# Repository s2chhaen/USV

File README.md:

Unmanned Surface Vehicle (USV)
# USV-Projekt

Im Projekt USV entwickeln Studenten unterschiedlicher Fachbereiche ein autonomes Wasserfahrzeug, welches eine vorgegebene Route fährt. Dabei müssen Kollisionen mit bewegten und unbewegten Hindernissen vermieden werden.

(c) 2023 Joe.G

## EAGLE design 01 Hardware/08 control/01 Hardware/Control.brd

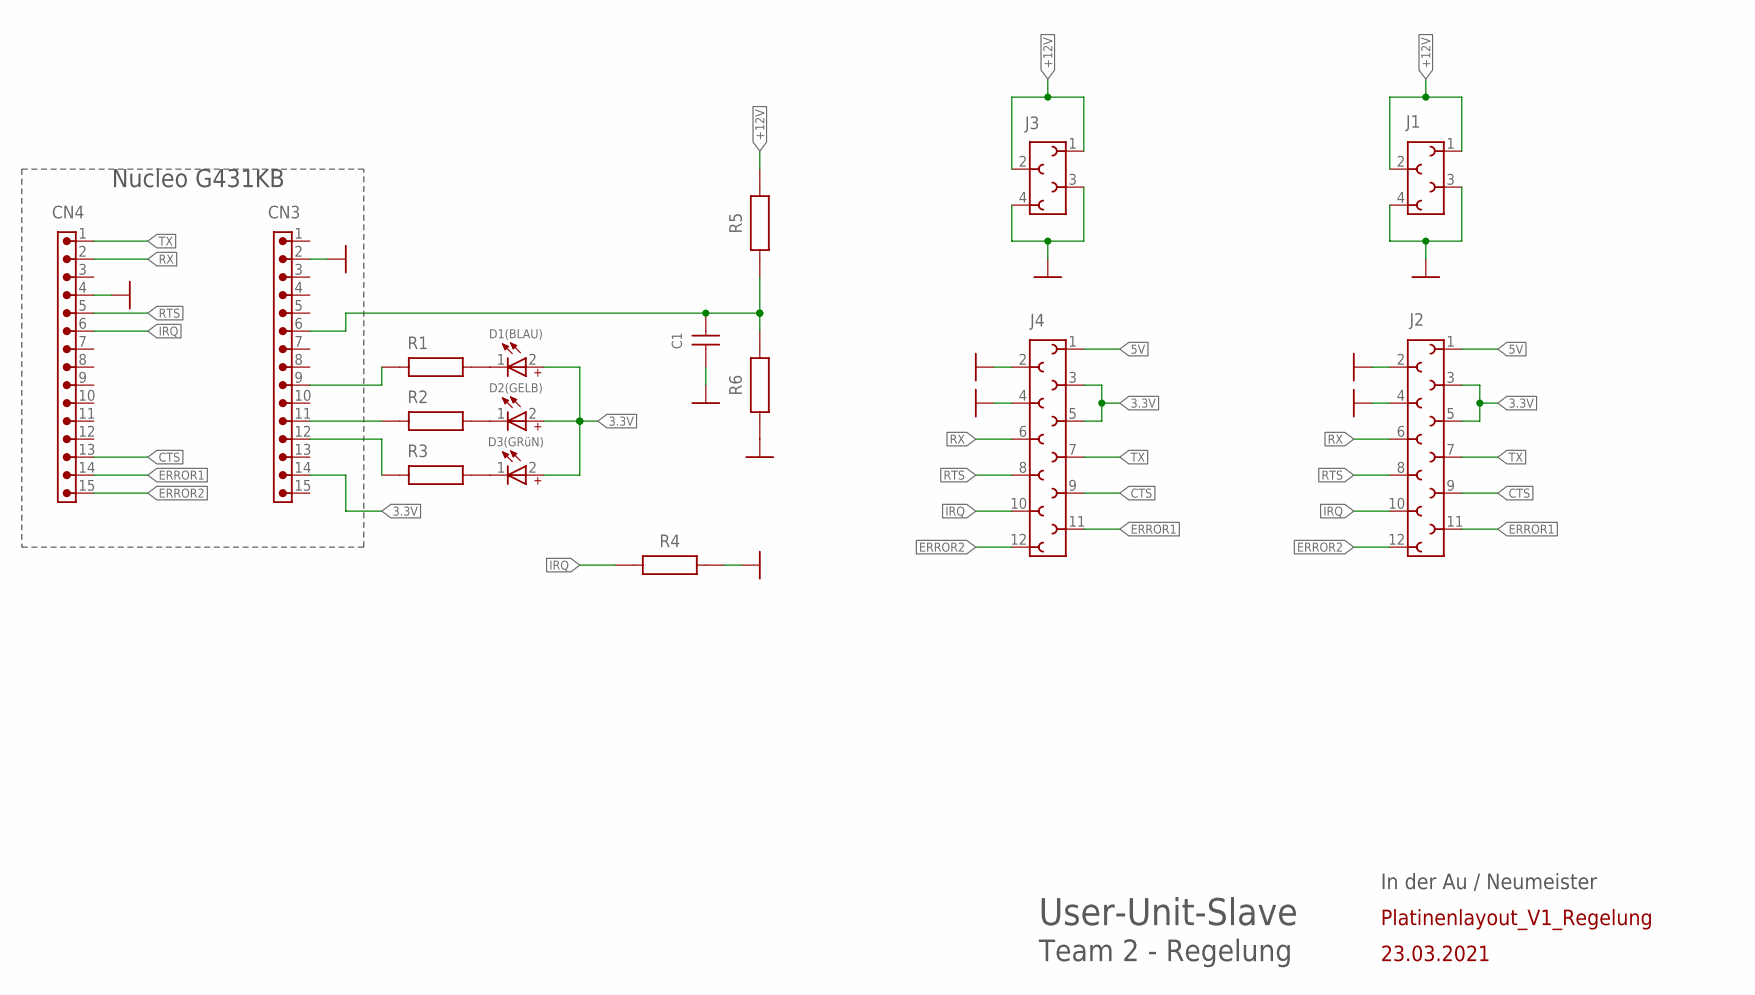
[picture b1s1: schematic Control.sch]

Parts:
C1: 10 nF; WCAP-CSGP_1206_H1.25
CN3, CN4: 61301511121
D1(BLAU): WL-TMRC_3MM_151031SS06000_WITHOUTSTOPPER; WL-TMRC_3MM
D2(GELB): WL-TMRC_3MM_151031YS06000_WITHOUTSTOPPER; WL-TMRC_3MM
D3(GRüN): WL-TMRC_3MM_151031VS06000_WITHOUTSTOPPER; WL-TMRC_3MM
J1: 6100XX11921_61000411921; 61000411921
J2: 6100XX11921_61001211921; 61001211921
J3: 690367290476
J4: 690367291276
R1, R2, R3, R5, R6: 1Ohm; WRIS-KSKE_0805_2.0X1.25X0.6(LXWXH)
R4: 0.1Ohm; WRIS-KSKE_0805_2.0X1.25X0.6(LXWXH)

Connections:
3.3V: CN3.14, D1(BLAU).2 (+), D2(GELB).2 (+), D3(GRüN).2 (+), J2.3, J2.5, J4.3, J4.5
5V: J2.1, J4.1
+12V: J1.1, J1.2, J3.1, J3.2, R5.2
ADC-INPUT: C1.2, CN3.6, R5.1, R6.2
CTS: CN4.13, J2.9, J4.9
ERROR1: CN4.14, J2.11, J4.11
ERROR2: CN4.15, J2.12, J4.12
GND: C1.1, CN3.2, CN4.4, J1.3, J1.4, J2.2, J2.4, J3.3, J3.4, J4.2, J4.4, R4.2, R6.1
GPIO_D1: CN3.9, R1.1
GPIO_D2: CN3.11, R2.1
GPIO_D3: CN3.12, R3.1
IRQ: CN4.6, J2.10, J4.10, R4.1
unnamed: D1(BLAU).1 (-), R1.2
unnamed: D2(GELB).1 (-), R2.2
unnamed: D3(GRüN).1 (-), R3.2
RTS: CN4.5, J2.8, J4.8
RX: CN4.2, J2.6, J4.6
TX: CN4.1, J2.7, J4.7

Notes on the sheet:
Nucleo G431KB
Team 2 - Regelung
User-Unit-Slave
In der Au / Neumeister
Platinenlayout_V1_Regelung
23.03.2021

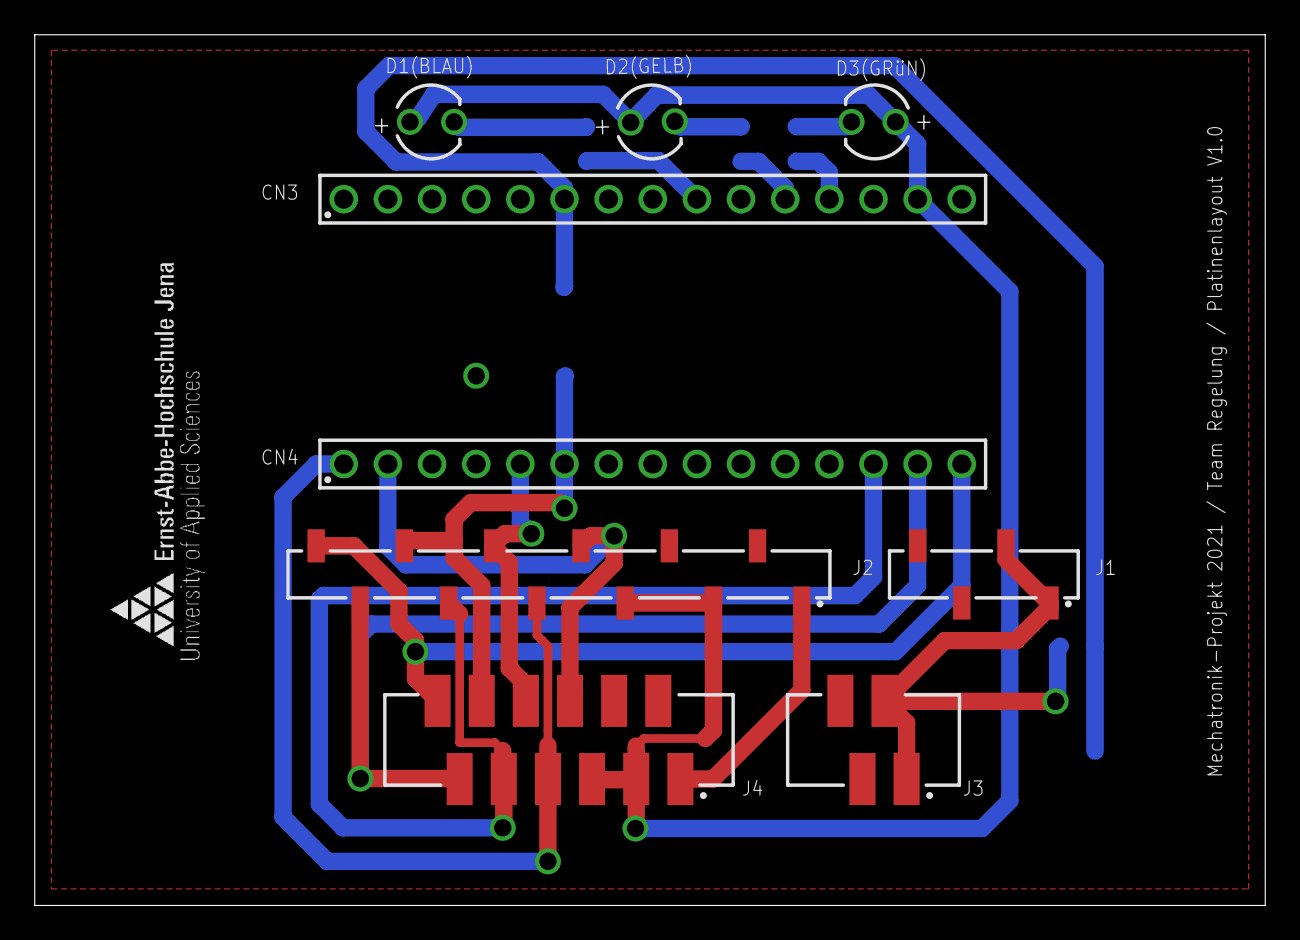
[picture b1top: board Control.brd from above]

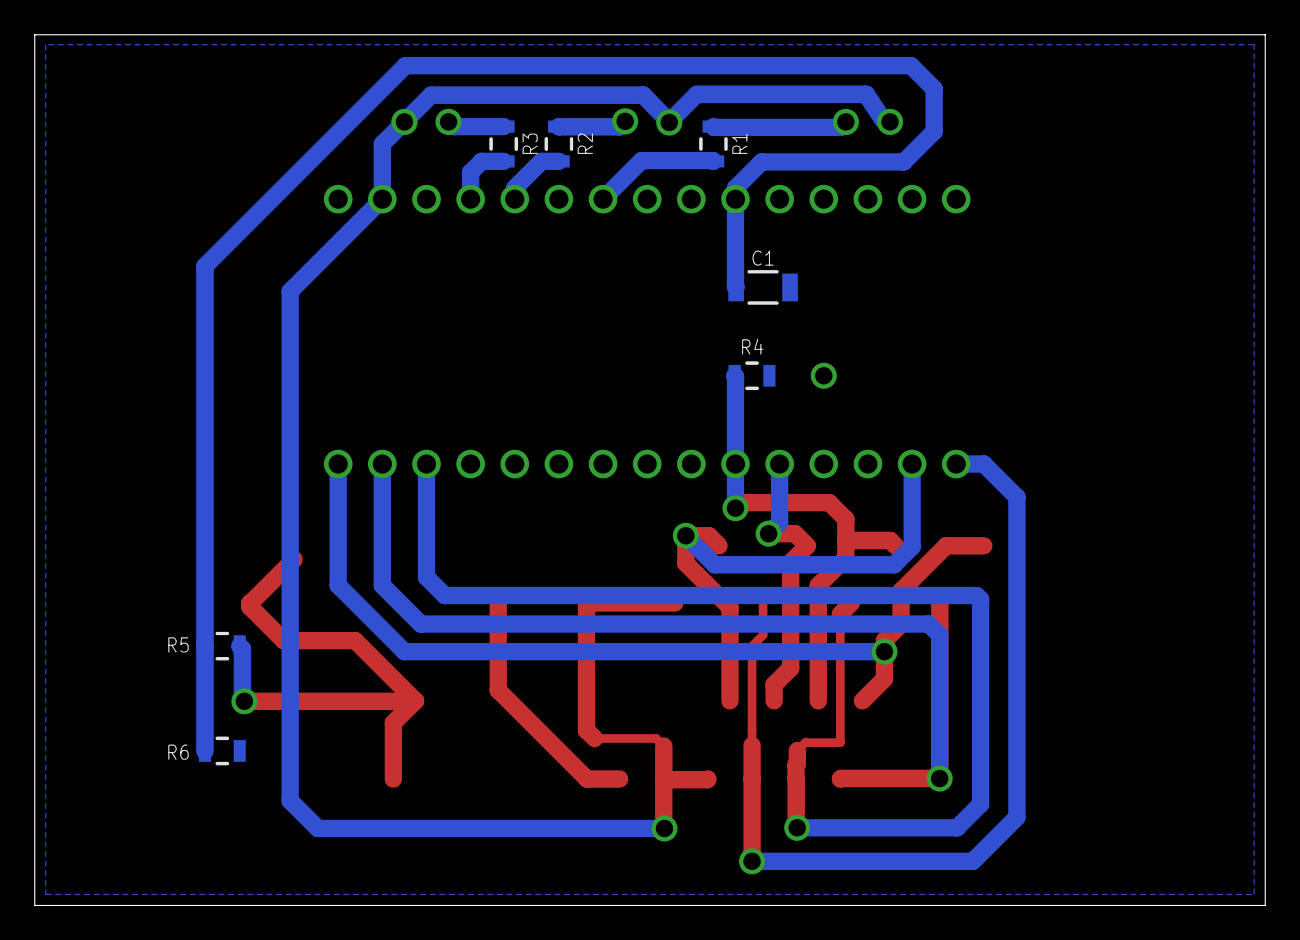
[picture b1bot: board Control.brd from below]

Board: 2 copper layers, 70.8 x 50.1 mm, 16 parts (7 on the bottom side), 18 nets.

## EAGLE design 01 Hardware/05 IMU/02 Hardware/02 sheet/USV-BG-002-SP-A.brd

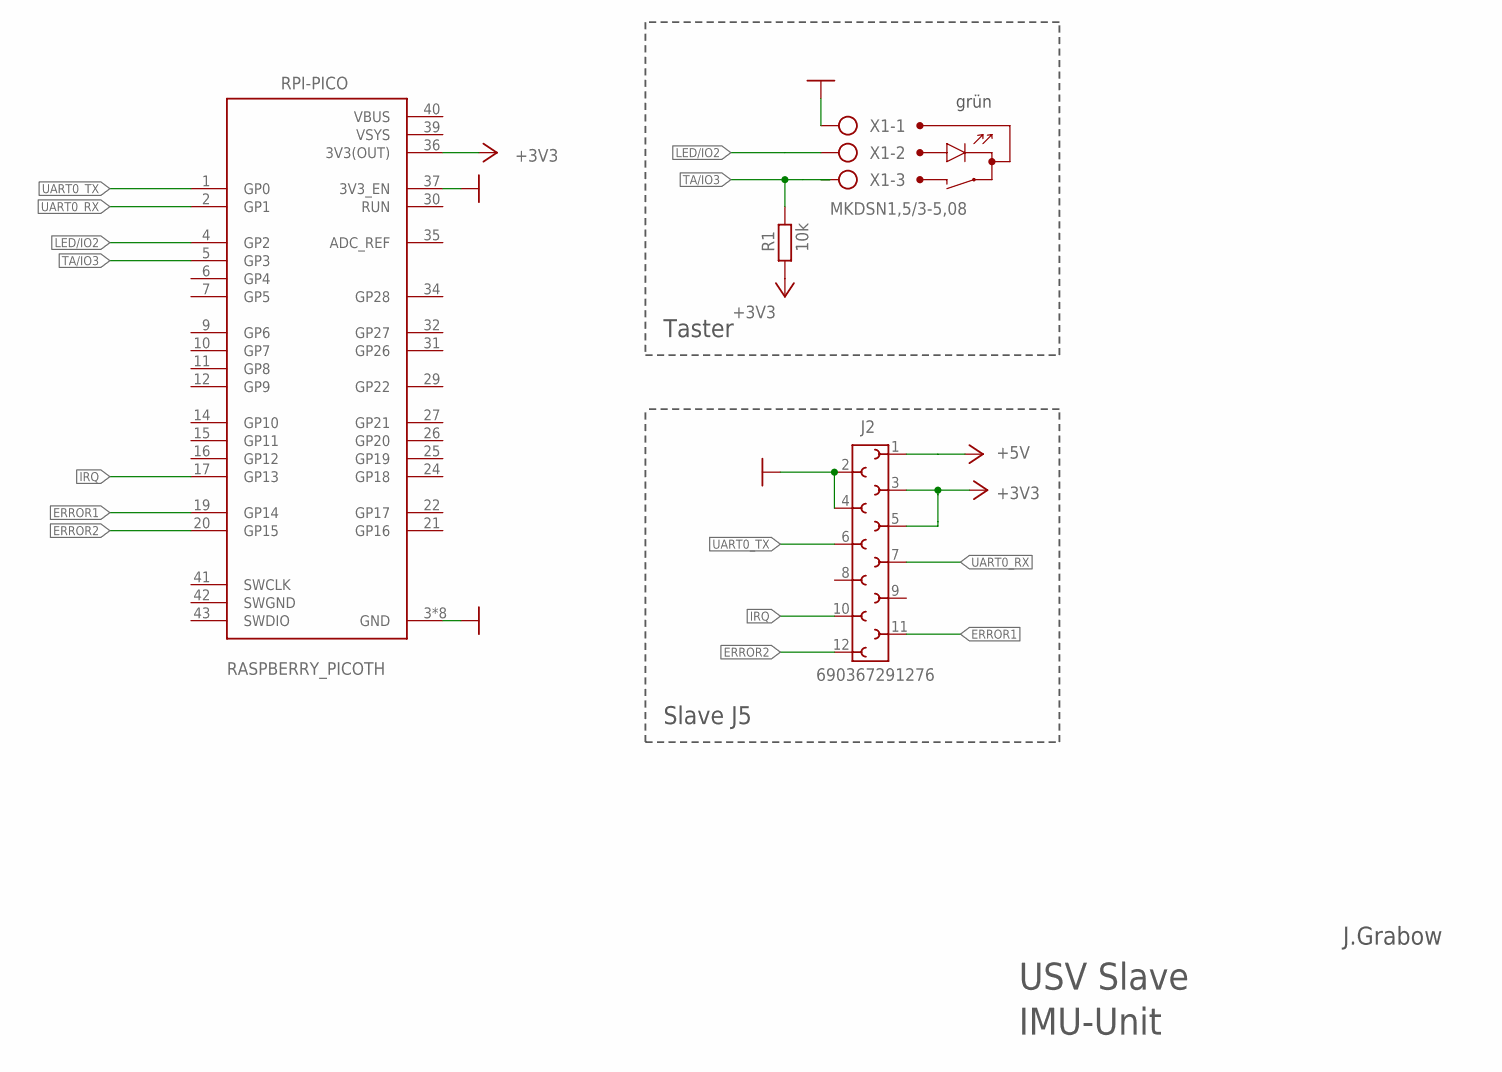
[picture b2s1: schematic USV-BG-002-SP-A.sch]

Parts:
J2: 690367291276
R1: 10k; M0805
RPI-PICO: RASPBERRY_PICOTH; PICO-PKG-TH
X1: MKDSN1,5/3-5,08

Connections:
+3V3: J2.3, J2.5, R1.1, RPI-PICO.36 (3V3(OUT))
+5V: J2.1
ERROR1: J2.11, RPI-PICO.19 (GP14)
ERROR2: J2.12, RPI-PICO.20 (GP15)
GND: J2.2, J2.4, RPI-PICO.3 (GND), RPI-PICO.8 (GND), RPI-PICO.13 (GND), RPI-PICO.18 (GND), RPI-PICO.23 (GND), RPI-PICO.28 (GND), RPI-PICO.33 (GND), RPI-PICO.37 (3V3_EN), RPI-PICO.38 (GND), X1.1
IRQ: J2.10, RPI-PICO.17 (GP13)
LED/IO2: RPI-PICO.4 (GP2), X1.2
SWGND: RPI-PICO.42 (SWGND)
TA/IO3: R1.2, RPI-PICO.5 (GP3), X1.3
UART0_RX: J2.7, RPI-PICO.2 (GP1)
UART0_TX: J2.6, RPI-PICO.1 (GP0)
VBUS: RPI-PICO.40 (VBUS)
VSYS: RPI-PICO.39 (VSYS)

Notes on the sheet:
Taster
IMU-Unit
USV Slave
J.Grabow
Slave J5
grün

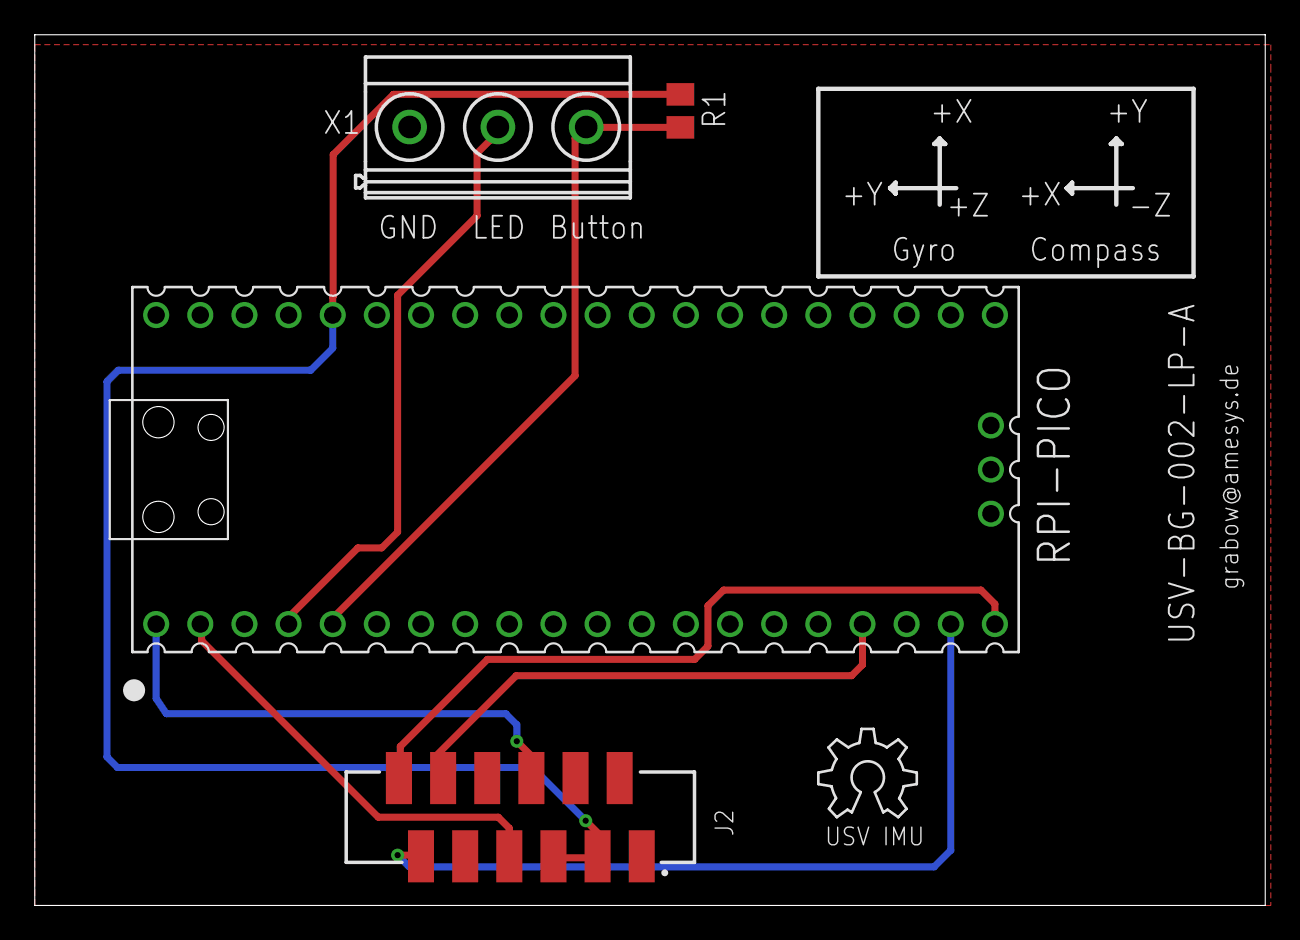
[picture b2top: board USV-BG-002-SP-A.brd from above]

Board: 2 copper layers, 70.8 x 50.1 mm, 5 parts (0 on the bottom side), 9 nets.

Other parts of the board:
U$1: OSHW_6X200_NOTEXT

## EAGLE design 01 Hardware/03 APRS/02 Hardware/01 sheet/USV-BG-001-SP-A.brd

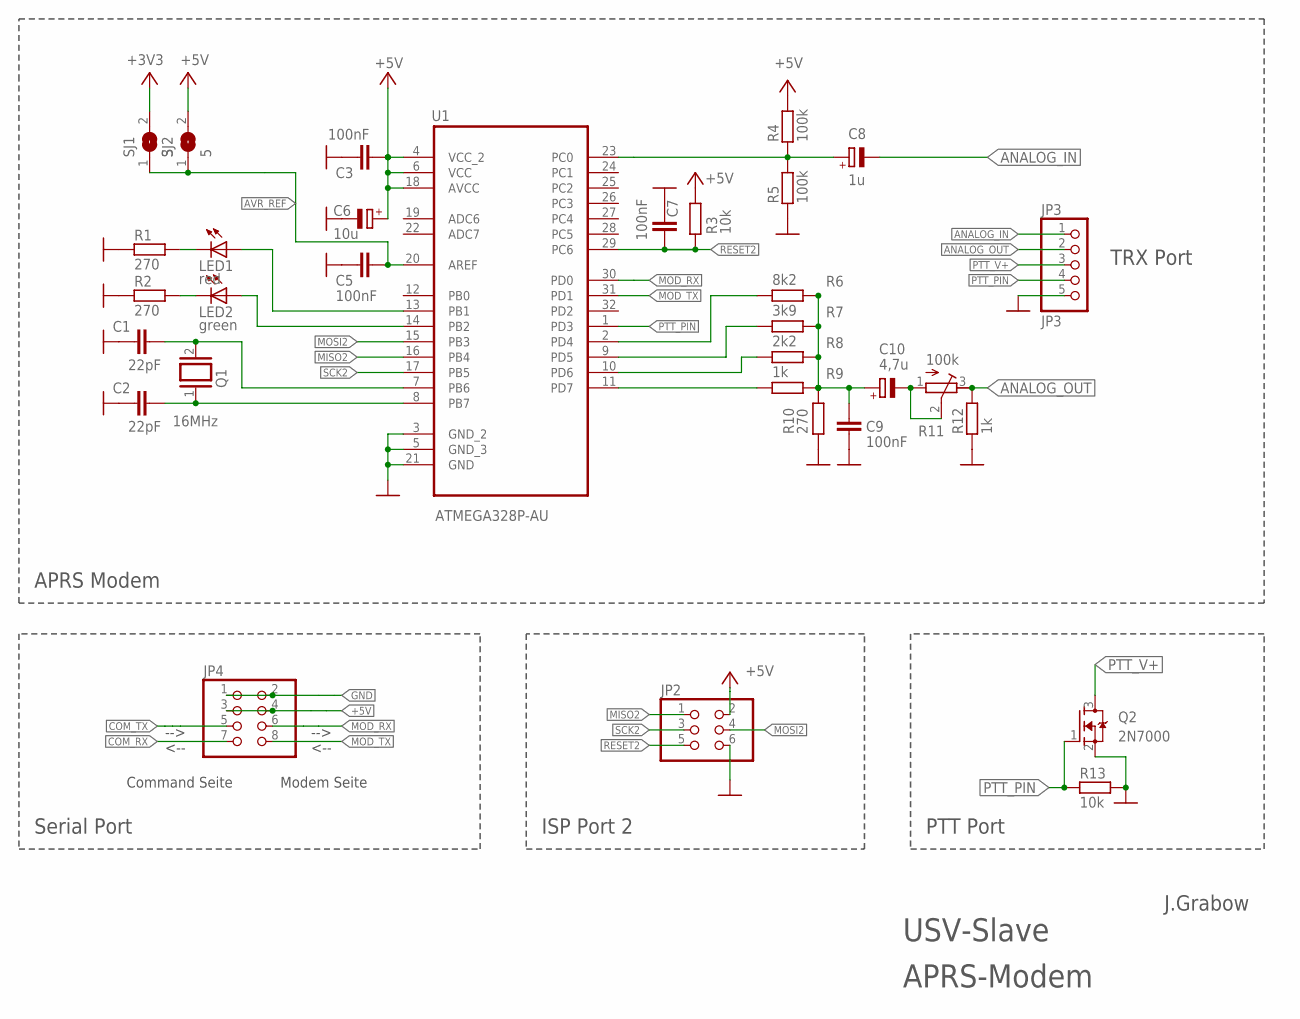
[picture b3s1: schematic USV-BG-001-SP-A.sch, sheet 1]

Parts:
C1, C2: 22pF; C0805
C3, C5, C7, C9: 100nF; C0805
C6: 10u; SMC_B
C8: 1u; SMC_B
C10: 4,7u; SMC_B
JP2: PINHD-2X3; 2X03
JP3: JP3; 1X05
JP4: PINHD-2X4; 2X04
LED1: red; LED_1206
LED2: green; LED_1206
Q1: 16MHz; QS
Q2: 2N7000; SOT23
R1, R2, R10: 270; R0805
R3, R13: 10k; R0805
R4, R5: 100k; R0805
R6: 8k2; R0805
R7: 3k9; R0805
R8: 2k2; R0805
R9, R12: 1k; R0805
R11: 100k; RTRIM3339P
SJ1: 3; SJ
SJ2: 5; SJ
U1: ATMEGA328P-AU; QFP80P900X900X120-32N

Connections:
+3V3: SJ1.2; also elsewhere on the board
+5V: C3.2, C6.+, JP2.2, JP4.3, JP4.4, R3.1, R4.2, SJ2.2, U1.4 (VCC_2), U1.6 (VCC), U1.18 (AVCC); also elsewhere on the board
ADC0: C8.+, R4.1, R5.2, U1.23 (PC0)
ANALOG_IN: C8.-, JP3.1
ANALOG_OUT: JP3.2, R11.3 (E), R12.2
AVR_REF: C5.2, SJ1.1, SJ2.1, U1.20 (AREF)
COM_RX: JP4.7; also elsewhere on the board
COM_TX: JP4.5; also elsewhere on the board
DAC_1: R6.2, U1.2 (PD4)
DAC_2: R7.2, U1.9 (PD5)
DAC_3: R8.2, U1.10 (PD6)
DAC_4: R9.2, U1.11 (PD7)
GND: C1.2, C2.2, C3.1, C5.1, C6.-, C7.1, C9.2, JP2.6, JP3.5, JP4.1, JP4.2, Q2.2 (S), R1.1, R2.1, R5.1, R10.1, R12.1, R13.2, U1.3 (GND_2), U1.5 (GND_3), U1.21 (GND); also elsewhere on the board
MISO2: JP2.1, U1.16 (PB4)
MOD_RX: JP4.6, U1.30 (PD0)
MOD_TX: JP4.8, U1.31 (PD1)
MOSI2: JP2.4, U1.15 (PB3)
unnamed: C1.1, Q1.2, U1.7 (PB6)
unnamed: C9.1, C10.+, R6.1, R7.1, R8.1, R9.1, R10.2
unnamed: LED2.C, R2.2
unnamed: LED2.A, U1.14 (PB2)
unnamed: C10.-, R11.1 (A), R11.2 (S)
unnamed: LED1.A, U1.13 (PB1)
unnamed: C2.1, Q1.1, U1.8 (PB7)
unnamed: LED1.C, R1.2
PTT_PIN: JP3.4, Q2.1 (G), R13.1, U1.1 (PD3)
PTT_V+: JP3.3, Q2.3 (D)
RESET2: C7.2, JP2.5, R3.2, U1.29 (PC6)
SCK2: JP2.3, U1.17 (PB5)

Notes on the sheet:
Modem Seite
Command Seite
Serial Port
ISP Port 2
PTT Port
APRS Modem
TRX Port
APRS-Modem
J.Grabow
-->
<--
USV-Slave

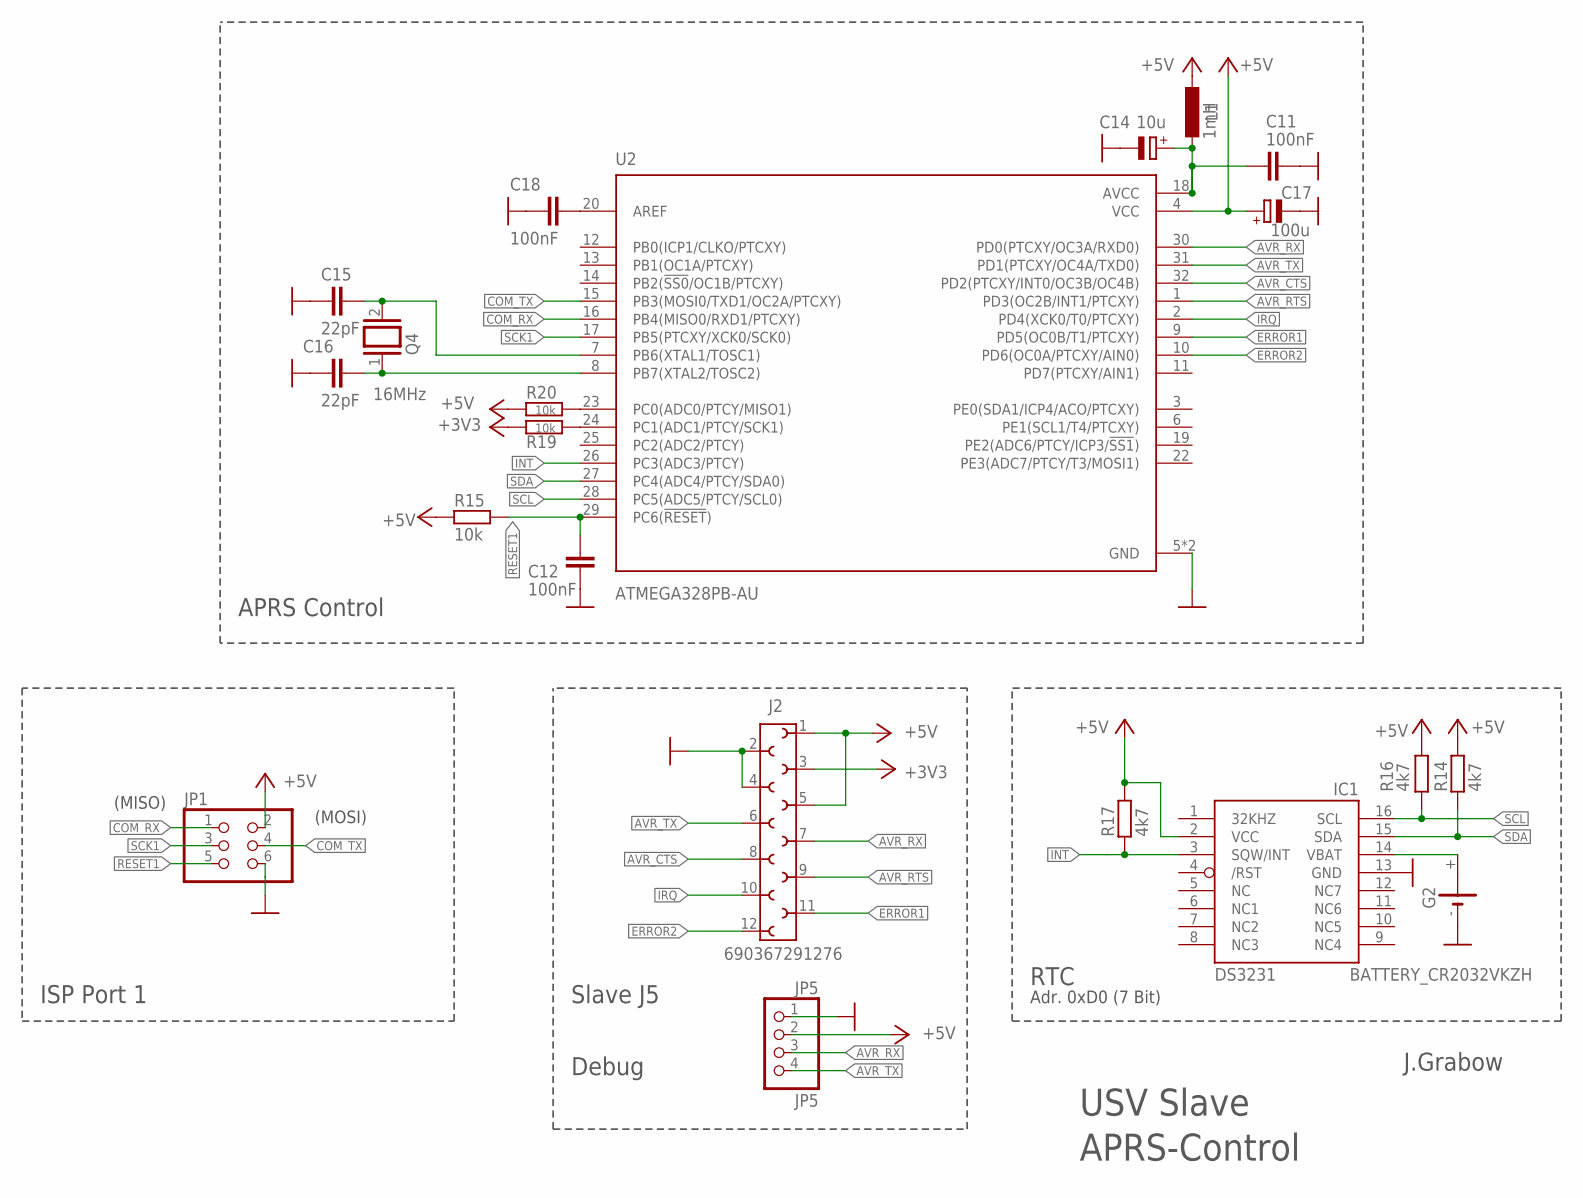
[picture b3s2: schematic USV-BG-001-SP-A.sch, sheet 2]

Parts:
C11, C12, C18: 100nF; C0805
C14: 10u; SMC_B
C15, C16: 22pF; C0805
C17: 100u; SMC_B
G2: BATTERY_CR2032VKZH; BATTERY_KZH20PCB-V
IC1: DS3231/SO; SO16W
J2: 690367291276
JP1: PINHD-2X3; 2X03
JP5: JP5; 1X04
L1: 1mH; L1812
Q4: 16MHz; QS
R14, R16, R17: 4k7; R0805
R15, R19, R20: 10k; R0805
U2: ATMEGA328PB-AU; QFP80P900X900X120-32N

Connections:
+3V3: J2.3, R19.1; also elsewhere on the board
+5V: C17.+, IC1.2 (VCC), J2.1, J2.5, JP1.2, JP5.2, L1.1, R14.2, R15.1, R16.2, R17.2, R20.1, U2.4 (VCC); also elsewhere on the board
AVR_CTS: J2.8, U2.32 (PD2(PTCXY/INT0/OC3B/OC4B))
AVR_RTS: J2.9, U2.1 (PD3(OC2B/INT1/PTCXY))
AVR_RX: J2.7, JP5.3, U2.30 (PD0(PTCXY/OC3A/RXD0))
AVR_TX: J2.6, JP5.4, U2.31 (PD1(PTCXY/OC4A/TXD0))
COM_RX: JP1.1, U2.16 (PB4(MISO0/RXD1/PTCXY)); also elsewhere on the board
COM_TX: JP1.4, U2.15 (PB3(MOSI0/TXD1/OC2A/PTCXY)); also elsewhere on the board
ERROR1: J2.11, U2.9 (PD5(OC0B/T1/PTCXY))
ERROR2: J2.12, U2.10 (PD6(OC0A/PTCXY/AIN0))
GND: C11.2, C12.2, C14.-, C15.2, C16.2, C17.-, C18.1, G2.-, IC1.13 (GND), J2.2, J2.4, JP1.6, JP5.1, U2.5 (GND), U2.21 (GND); also elsewhere on the board
INT: IC1.3 (SQW/INT), R17.1, U2.26 (PC3(ADC3/PTCY))
IRQ: J2.10, U2.2 (PD4(XCK0/T0/PTCXY))
unnamed: C16.1, Q4.1, U2.8 (PB7(XTAL2/TOSC2))
unnamed: C15.1, Q4.2, U2.7 (PB6(XTAL1/TOSC1))
unnamed: G2.+, IC1.14 (VBAT)
unnamed: C11.1, C14.+, L1.2, U2.18 (AVCC)
unnamed: C18.2, U2.20 (AREF)
unnamed: R20.2, U2.23 (PC0(ADC0/PTCY/MISO1))
unnamed: R19.2, U2.24 (PC1(ADC1/PTCY/SCK1))
RESET1: C12.1, JP1.5, R15.2, U2.29 (PC6(!RESET!))
SCK1: JP1.3, U2.17 (PB5(PTCXY/XCK0/SCK0))
SCL: IC1.16 (SCL), R16.1, U2.28 (PC5(ADC5/PTCY/SCL0))
SDA: IC1.15 (SDA), R14.1, U2.27 (PC4(ADC4/PTCY/SDA0))

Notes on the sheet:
ISP Port 1
(MOSI)
(MISO)
APRS-Control
USV Slave
J.Grabow
Slave J5
APRS Control
RTC
Adr. 0xD0 (7 Bit)
Debug

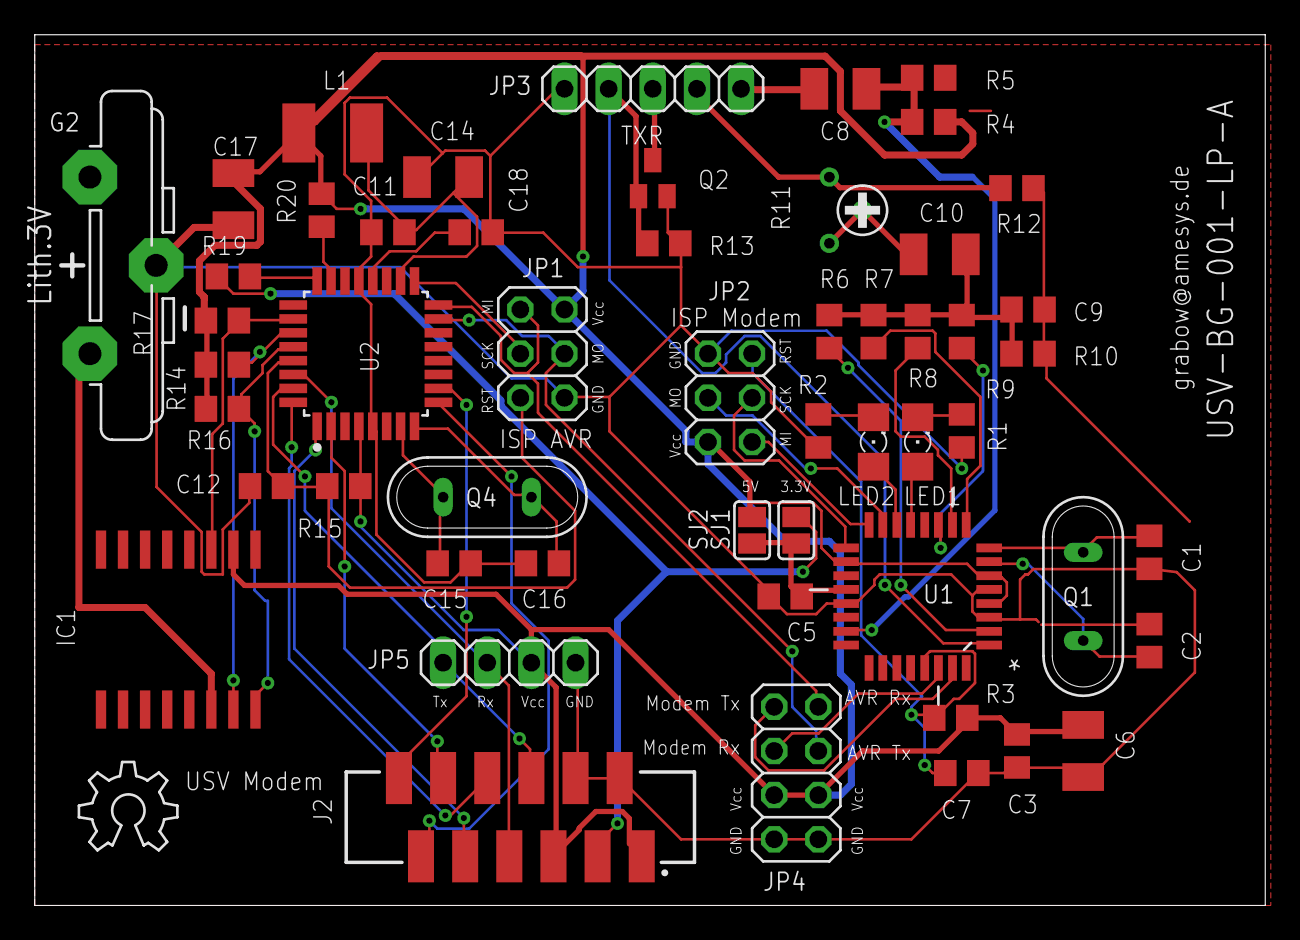
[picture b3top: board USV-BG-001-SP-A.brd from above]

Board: 2 copper layers, 70.8 x 50.1 mm, 54 parts (0 on the bottom side), 48 nets.

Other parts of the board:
U$1: OSHW_6X200_NOTEXT

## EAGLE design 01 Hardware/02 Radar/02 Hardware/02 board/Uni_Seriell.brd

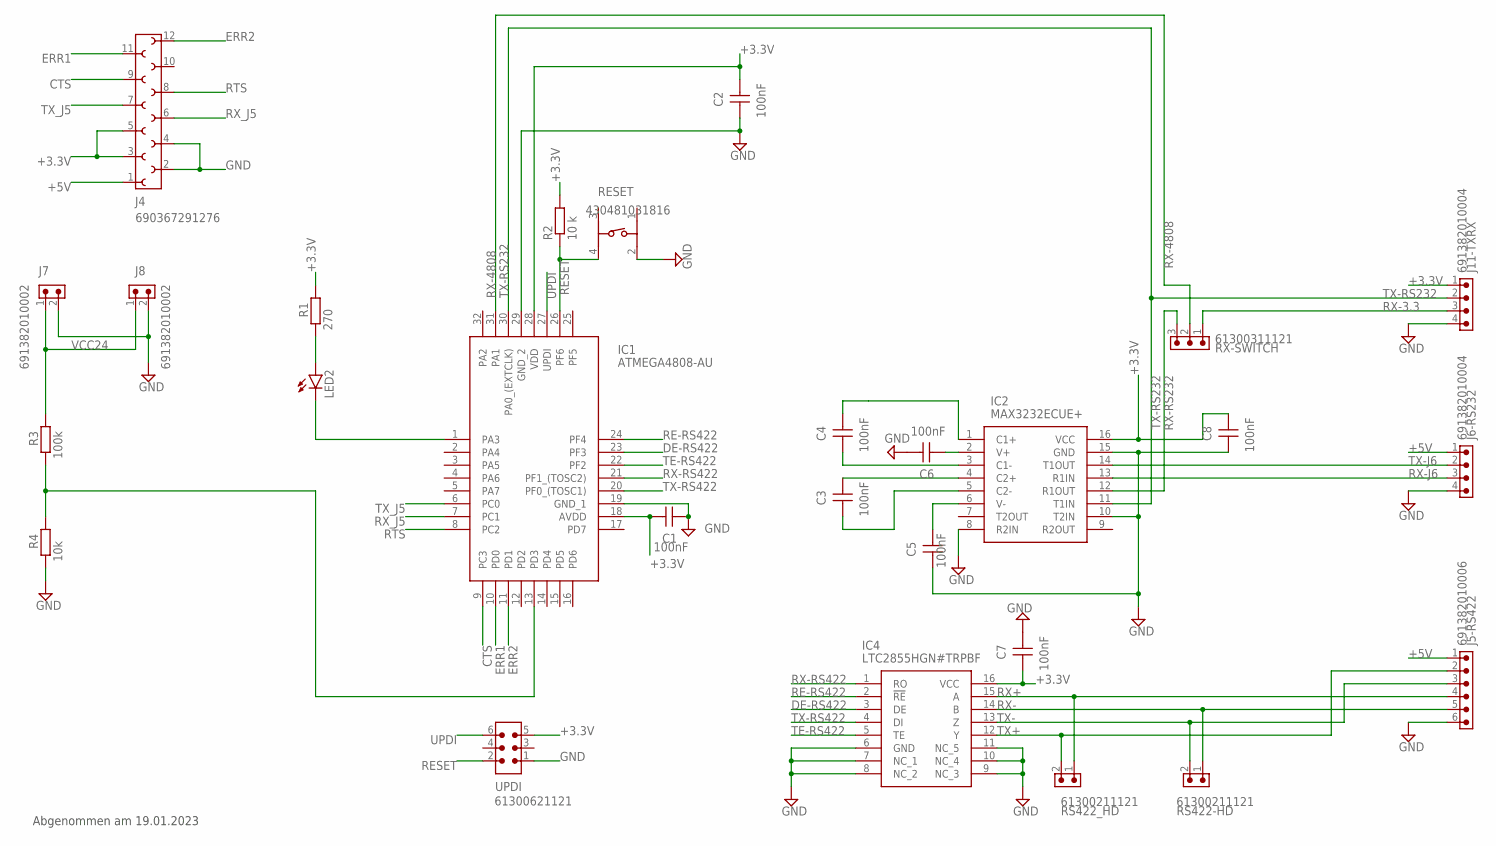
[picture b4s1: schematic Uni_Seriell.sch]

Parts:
C1, C2, C3, C4, C5, C6, C7, C8: 100nF; WCAP-CSST_0805
IC1: ATMEGA4808-AU; QFP80P900X900X120-32N
IC2: MAX3232ECUE+; SOP65P640X110-16N
IC4: LTC2855HGN#TRPBF; SOP64P601X175-16N
J4: 690367291276
J5-RS422: 691382010006
J6-RS232, J11-TXRX: 691382010004
J7, J8: 691382010002
LED2: LEDCHIP-LED0805; CHIP-LED0805
R1: 270; R0805
R2: 10 k; R0805
R3: 100k; R0805
R4: 10k; R0805
RESET: 430481031816
RS422-HD, RS422_HD: 61300211121
RX-SWITCH: 61300311121
UPDI: 61300621121

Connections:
+3.3V: C1.2, C2.2, C7.1, C8.2, IC1.18 (AVDD), IC1.28 (VDD), IC2.16 (VCC), IC4.16 (VCC), J4.3, J4.5, J11-TXRX.1, R1.2, R2.2, UPDI.5
+5V: J4.1, J5-RS422.1, J6-RS232.1
CTS: IC1.9 (PC3), J4.9
DE-RS422: IC1.23 (PF3), IC4.3 (DE)
ERR1: IC1.10 (PD0), J4.11
ERR2: IC1.11 (PD1), J4.12
GND: C1.1, C2.1, C5.1, C6.2, C7.2, C8.1, IC1.19 (GND_1), IC1.29 (GND_2), IC2.8 (R2IN), IC2.10 (T2IN), IC2.15 (GND), IC4.6 (GND), IC4.7 (NC_1), IC4.8 (NC_2), IC4.9 (NC_3), IC4.10 (NC_4), IC4.11 (NC_5), J4.2, J4.4, J5-RS422.6, J6-RS232.4, J7.2, J8.2, J11-TXRX.4, R4.1, RESET.2, UPDI.1
unnamed: IC1.13 (PD3), R3.1, R4.2
unnamed: IC1.1 (PA3), LED2.C
unnamed: LED2.A, R1.1
unnamed: C5.2, IC2.6 (V-)
unnamed: C6.1, IC2.2 (V+)
unnamed: C3.2, IC2.4 (C2+)
unnamed: C3.1, IC2.5 (C2-)
unnamed: C4.1, IC2.3 (C1-)
unnamed: C4.2, IC2.1 (C1+)
RE-RS422: IC1.24 (PF4), IC4.2 (!RE)
RESET: IC1.26 (PF6), R2.1, RESET.4, UPDI.2
RTS: IC1.8 (PC2), J4.8
RX+: IC4.15 (A), J5-RS422.4, RS422_HD.1
RX-: IC4.14 (B), J5-RS422.5, RS422-HD.1
RX-3.3: J11-TXRX.3, RX-SWITCH.1
RX-4808: IC1.31 (PA1), RX-SWITCH.2
RX-J6: IC2.13 (R1IN), J6-RS232.3
RX-RS232: IC2.12 (R1OUT), RX-SWITCH.3
RX-RS422: IC1.21 (PF1_(TOSC2)), IC4.1 (RO)
RX_J5: IC1.7 (PC1), J4.6
TE-RS422: IC1.22 (PF2), IC4.5 (TE)
TX+: IC4.12 (Y), J5-RS422.2, RS422_HD.2
TX-: IC4.13 (Z), J5-RS422.3, RS422-HD.2
TX-J6: IC2.14 (T1OUT), J6-RS232.2
TX-RS232: IC1.30 (PA0_(EXTCLK)), IC2.11 (T1IN), J11-TXRX.2
TX-RS422: IC1.20 (PF0_(TOSC1)), IC4.4 (DI)
TX_J5: IC1.6 (PC0), J4.7
UPDI: IC1.27 (UPDI), UPDI.6
VCC24: J7.1, J8.1, R3.2

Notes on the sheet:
Abgenommen am 19.01.2023

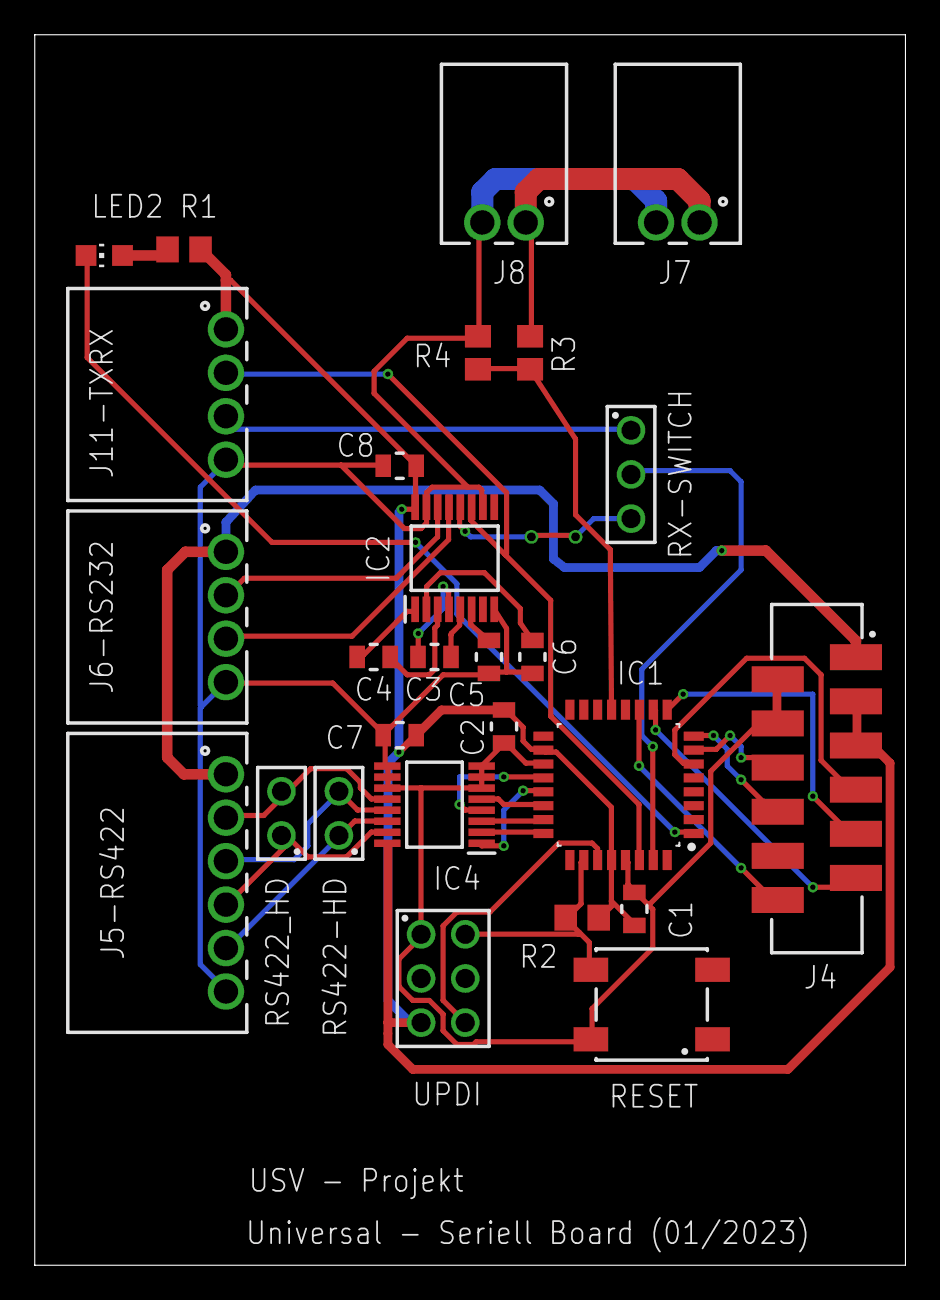
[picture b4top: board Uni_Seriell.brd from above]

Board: 2 copper layers, 50.1 x 70.8 mm, 27 parts (0 on the bottom side), 36 nets.

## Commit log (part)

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2024-02-04 comConfig.h: Hinzufüge der Header-Datei
2024-02-04 comConfig.h: Definition der Position der Zustand- und Daten-Flag im Register des Kommunikationskanals
2024-02-04 comConfig.h: Definition der Enumeration zum Markieren der Position des Programmablaufs
2024-02-04 timerUnit.h und timerUnit.c: Die Namen der Funktion und Variablen werden für RadarMain-Projekt angepasst. Sie sind ähnlich mit den im LidarMain-Projekt, nur die Funktions- und Variablenamen anders
2024-02-04 usvDataHandler.c: Hinzufüge der Source-Datei
2024-02-04 usvDataHandler.c: Funktion usv_ioStreamStatusAvai() angepasst mit RadarMain-Projekt angepasst
2024-02-04 usvDataHandler.c: Funktion usv_mainFsmStartSHandlerFunc() unverändert hinzugefügt
2024-02-04 usvDataHandler.c: Funktion usv_mainFsmStatusRspPollSHandlerFunc() unverändert hinzugefügt
2024-02-04 usvDataHandler.c: Funktion usv_mainFsmStatusRspCheckSHandlerFunc() refaktorisiert: mit RadarMain-Projekt angepasst
2024-02-04 usvDataHandler.c: Funktion usv_mainFsmDataRspCheckStateFunc() refaktorisiert: mit RadarMain-Projekt angepasst
2024-02-05 radarHandler.h: Hinzufüge der Header-Datei
2024-02-05 radarHandler.h: Inklusion der Header-Datei der HAL-Bibliothek
2024-02-05 radarHandler.h: Definition der Radar-bezogene Parameter
2024-02-05 radarHandler.h: Definition des Arbeitsmoduses vom Radar
2024-02-05 radarHandler.h: Definition der Radar-Datenempfangen-FSM
2024-02-05 radarHandler.h: Definition der Zustände für Haupt-FSM dieses Modul
2024-02-05 radarHandler.h: Definition der Eingabe-FIFO zum Speichern der Eingabe
2024-02-05 radarHandler.h: Definition der Struktur zur internen Verwaltung des Moduls
2024-02-05 radarHandler.h: Hinzufüge der Abkürzungsliste
2024-02-05 radarHandler.c: Deklaration der internen globalen Variablen zur Protokollbehandlung
2024-02-05 radarHandler.c: Deklaration der Verwaltungsvariablen
2024-02-05 radarHandler.c: Deklaration der Variablen zur Verwaltung der internen FSM
2024-02-05 radarHandler.c: Deklaration der Zustand-Handler-Routinen und Look-up-Tabelle für Datenempfangen-FSM
2024-02-05 radarHandler.c: Deklaration der Zustand-Hanlder-Routinen und Look-up-Tabelle für Modul-Haupt-FSM
2024-02-05 radarHandler.c: Implementation der Funktion checkFIFOEmptyState() hinzugefügt
2024-02-05 radarHandler.c: Hinzufüge der Implementation der Funktion getFIFOFreeSpace()
2024-02-05 radarHandler.c: Hinzufüge der Implementation der Funktion radar_ioStreamDataAvai()
2024-02-05 radarHandler.c: Hinzufüge der Implementation der Funktion searchNumFormatInStr() zur Erkennung der Position einer Nummerreihe in einer Zeichenfolge
2024-02-05 radarHandler.c: Hinzufüge der Implementation der Zustand-Handler-Routine für Radar-Datenempfangen-FSM
2024-02-05 radarHandler.c: Hinzufüge der Funktion radar_callbackTx() zum Rückruf in der USART-TX-ISR
2024-02-05 radarHandler.c: Hinzufüge der Implementation der Funktion radar_initDev()
2024-02-05 radarHandler.c: Hinzufüge der Abkürzungstabelle
2024-02-05 radarDataPrc.h: Inklusion der notwendigen System-Bibliothek-Header-Daten
2024-02-05 radarDataPrc.h: Hinzufüge der Deklaration der externen Funktion
2024-02-05 radarDataPrc.c: Hinzufüge der Source-Datei
2024-02-05 main.h: Hinzufüge der Header-Datei
2024-02-05 main.h: Inklusion der Header-Daten von Timer-Einheit, Radar-Handler-, USV-Data-Handler- und Datenverarbeitungseinheit
2024-02-05 main.c: Hinzufüge der Implementation des Programmsablaufs
2024-02-05 Umbenennung von test1.m zu test0.m
2024-02-05 test2.m: Hinzufüge der Beschreibung und Kommentare
2024-02-05 test2.m: Wert von Variablen draw verändert
2024-02-05 filterIIR.m: Funktion filterIIR() refaktorisiert: Namen und Typ des letzten Arguments verändert, Hinzufüge der Namen für die Abbildung
2024-02-05 test2.m: Löschen der figureNo Variable und seine Anwesenheit in der Quellcode
2024-02-05 Umbenennung test2.m zu test1.m
2024-02-05 test1.m: Name der Achsen hinzugefügt
2024-02-05 test3.m: Hinzufüge der Namen sowie der Achsennamen des Originalsignaldiagramms
2024-02-05 test3.m: Zusammenpacken der draw Variable an nur eine Stelle
2024-02-05 Umbenennung test3.m in test2.m
2024-02-05 test4.m: Verbesserung der Kommentare
2024-02-05 test1.m: Korrektur der Rechtschreibung im Diagramm
2024-02-05 test4.m: Löschen der figureNo Variable
2024-02-05 test4.m: Korrektur der Nummer des Versuches
2024-02-05 test0.m: Anpassung mit der neuen Funktion filterIIR() und filterFIR()
2024-02-05 test1.m: Hinzufüge des Dokumentationsabschnittes
2024-02-05 test3.m: Hinzufüge des Dokumentationsabschnittes
2024-02-05 filterOrder.m: Korrektur der Formel
2024-02-05 test0.m: Hinzufüge der Beschreibung
2024-02-05 Löschen der nicht mehr notwendigen Daten
2024-02-05 main.m: Berechnung der Abtastfrequenz unter Anwendung der Funktion filterSampleFreq()
2024-02-05 Anpassung mit der neuen filterSampleFreq()
2024-02-06 asciiTable.h: Beschreibung hinzugefügt
2024-02-06 usvDataHandler.h: Hinzufüge der Beschreibung
2024-02-06 usvDataHandler.c: Dokumentation refaktorisiert: Korrektur der Beschreibung und Ausgabe
2024-02-06 usvDataHandler.c: getRegLen() refaktorisiert: die Länge von ER4_ADD verkürzt
2024-02-06 lidarHandler.c: Korrektur der Definition der Zustand-Register-Länge
2024-02-06 lidarHandler.c: lidar_paramStartSHandlerFunc() refaktorisiert: Anpassung mit der neuen Struktur von Variable lidar_status (deren Typ lidarStatus_t ist)
2024-02-06 lidarHandler.c: lidar_mainDataCheckSHandler() refaktorisiert: Anpassung mit der neuen Struktur von Variable lidar_status (deren Typ lidarStatus_t ist)
2024-02-06 main.c: Darstellung verbessert
2024-02-06 usvDataHandler.c: Funktion checkRxData() dokumentiert
2024-02-06 usvDataHandler.c: Dokumentation der Funktion usv_ioStreamStatusAvai() hinzugefügt
2024-02-06 usvDataHandler.c: Hinzufüge der Dokumentation der Funktion usv_setProtocol()
2024-02-06 usvDataHandler.c: Dokumentation der Funktion usv_setRegister()
2024-02-06 usvDataHandler.c: Dokumentation der Funktion fsm_setterRxStateHandlerFunc()
2024-02-06 usvDataHandler.c: Dokumentation der Funktion fsm_setterEndSHandlerFunc() hinzugefügt
2024-02-06 usvDataHandler.c: Dokumentation der Funktionen usv_mainFsmStatusTxSHandlerFunc(), usv_mainFsmStatusRspPollSHandlerFunc() und usv_mainFsmStatusRspCheckSHandlerFunc() hinzugefügt
2024-02-07 usvDataHandler.c: Dokumentation der Funktion usv_mainFsmDataRspPollSHandlerFunc()
2024-02-07 usvDataHandler.c: Dokumentation der Funktion usv_mainFsmErrorSHandlerFunc()
2024-02-07 usvDataHandler.c: Dokumentation der Funktion usartCallbackTx() refaktorisiert: Korrektur der Fehler beim Argument data
2024-02-07 usvDataHandler.c: Dokumentation der Funktion usv_setAddr()
2024-02-07 timerUnit.c: Hinzufüge der Beschreibung
2024-02-07 timerUnit.c: Dokumentation aller Funktionen zum Steuern des USV-Data-Wächter
2024-02-07 registerModel.h: Hinzufüge der Beschreibung
2024-02-07 main.h: Beschreibung hinzugefügt
2024-02-07 lidarHandlerProtocol.h: Hinzufüge der Beschreibung
2024-02-07 lidarDataPrc.c: Beschreibung hinzugefügt
2024-02-07 MQTT to MariaDB
2024-02-07 Readme Software
2024-02-07 Readme MQTT Dokumentation
2024-02-07 lidarDataPrc.c: Dokumentation der Funktion fil_init()
2024-02-07 lidarDataPrc.c: Dokumentation der Funktion fil_convertData()
2024-02-07 lidarDataPrc.c: Dokumentation der Funktion redundacyAdd()
2024-02-07 lidarDataPrc.c: Dokumentation der Funktion shiftPhaseCompensation()
2024-02-07 lidarDataPrc.c: Dokumentation der Funktion fil_compressNReturn()
2024-02-07 lidarHandler.c: Beschreibung hinzugefügt
2024-02-07 lidarHandler.c: Dokumentation der Funktion lidar_rspVal() hinzugefügt
2024-02-07 lidarHandler.c: Dokumentation der Funktion lidar_checkRXData()
2024-02-07 lidarHandler.c: Dokumentation der Funktion lidar_dataCheck()
2024-02-07 lidarHandler.c: Dokumentation der Funktion lidar_setProtocol()
2024-02-07 lidarHandler.c: Dokumentation der Funktion lidar_ioStreamStatusAvai()
2024-02-07 lidarHandler.c: Dokumentation der Funktion lidar_dataGet()
2024-02-07 lidarHandler.c: Dokumentation aller Zustand-Handler-Routinen der Rücksetzen-FSM hinzugefügt
2024-02-07 lidarHandler.c: Aktualisieren der Dokumentation über den Pause-Zustand aller internen FSMs
2024-02-07 lidarHandler.c: Dokumentation der Rückruffunktion lidar_callbackTx() hinzugeüfgt
2024-02-07 lidarHandler.c: Dokumentation der Funktion lidar_initDev() hinzugefügt
2024-02-07 lidarHandler.c: Dokumentation der Funktion lidar_setAddr()
2024-02-07 comConfig.h: Beschreibung, Version und Revision und Korrektur der Rechtschreibung hinzugefügt
2024-02-07 usvDataHandler.h: Aktualisieren der Beschreibung, Revision und der Register-Adresse
2024-02-07 usvDataHandler.c: Dokumentation der Funktion getRegLen() refaktorisiert: Aktualisierung des Inhaltes
2024-02-07 usvDataHandler.c: Dokumentation der Funktion usv_ioStreamStatusAvai()
2024-02-07 usvDataHandler.c: Dokumentation der Funktion usv_setProtocol()
2024-02-07 usvDataHandler.c: Dokumentation aller Zustand-Handler-Routinen der Modul-Haupt-FSM
2024-02-07 usvDataHandler.c: Dokumentation von usartCallbackRx() refaktorisiert: Korrektur die Beschreibung des adress-Argumentes
2024-02-07 usvDataHandler.c: Dokumentation der Funktion usv_initDev() aktualisiert
2024-02-07 timerUnit.h: Hinzufüge der Beschreibung und Revision
2024-02-07 timerUnit.c: Hinzufüge der Dokumentation der Funktion timer_init()
2024-02-07 timerUnit.c: Hinzufüge der Dokumentation der Funktionen zum Steuern des Radar-Handler-Wätchers
2024-02-07 main.h: Hinzufüge der Beschreibung und Revision
2024-02-08 radarHandler.c: Dokumentation der Funktion checkFIFOFullState() hinzugefügt
2024-02-08 radarHandler.c: Hinzufüge der Beschreibung und Revision
2024-02-08 radarHandler.c: Dokumentation der Funktion getFIFOFreeSpace()
2024-02-08 radarHandler.c: Dokumentation der Funktion radar_ioStreamDataAvai()
2024-02-08 radarHandler.c: Dokumentation der Funktion searchNumFormatInStr()
2024-02-08 radarHandler.c: Hinzufüge der DOkumentation aller Zustand-Handler-Routinen der Datenempfangen-FSM
2024-02-08 radarHandler.c: Dokumentation der Zustand-Handler-Routinen der Datenempfangen-FSM
2024-02-08 radarHandler.c: Dokumentation der Funktion radar_callbackTx()
2024-02-08 radarHandler.c: Dokumentation der Funktion radar_initDev() hinzugefügt
2024-02-08 main.c: Beschreibung in Description umbenannt im Info-Teil
2024-02-08 radarHandler.c: Beschreibung in Description umbenannt im Info-Teil
2024-02-08 radarHandler.h: Beschreibung in Description umbenannt im Info-Teil
2024-02-08 radarDataPrc.c: Hinzufüge der Beschreibung und Revision
2024-02-08 filter_FIR.c: Entfernung aller nicht notwendigen Teile
2024-02-08 main.c: Löschen der Uhrzeit im Info-Teil
2024-02-08 filter_FIR.c: Hinzufüge des Info-Teils
2024-02-08 ioModul.c: Hinzufüge des Info-Teils
2024-02-08 ioModul.c: Dokumentation der Funktion readFile()
2024-02-08 ioModul.c: Dokumentation der Funktion writeFileInt32()
2024-02-08 ioModul.c: Dokumentation der Funktion writeFileInt32 aktualisieren
2024-02-08 filter_FIR.c: Dokumentation der Funktion fir_init()
2024-02-08 asciiTable.h und crcCalculator.c: Hinzufüge des Info-Teils
2024-02-08 Unbenennung des Ordners 02_Mikrocontroller in 03 Mikrocontroller
2024-02-08 Update Note.txt: Löschen der altmodischen Dokumentationen
2024-02-08 Löschen des "Inbetriebnahme USART"-Projekt, da es in main-Branch nicht notwendig ist
2024-02-08 Löschen des "Testen mit USVData"-Projektes, da sie in main-Branch nicht notwendig ist
2024-04-08 IMU Data
2024-07-01 USV-SQL MariaDB
2024-07-02 Datenfluss
2024-07-02 Grafana-Dashboard
2024-07-11 digitaler Zwilling
2024-07-11 Beschreibung Bussystem
2024-07-12 Datenblock
2024-07-16 MQTT to SQL Tool
2024-07-16 MQTT Servive
2024-07-18 Flowchart
2024-07-18 Grafana
2024-07-18 Rename Grafana.png to Grafana_bak.png
2024-08-02 drive
2024-10-10 RPi Pico PIO Modul für UART
2024-10-16 Kommunikationsstruktur
2024-10-16 Futaba SBUS Driver
2024-10-16 function for drive(trust,rudder)
2024-10-17 new overview of the drives
2024-11-14 GPS-logging
2024-11-20 Datenblock erweitert (Lichterführung)
2024-11-20 Datablock (Lichterführung)
2024-11-21 - append 'USV Bus Ethernet bridge' project to '01 Hardware' - Version 01.10 - include a WLAN class for automatic connect and reconnect with network time protocol to get the system time - include a st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
2024-11-25 Lichterführung
2026-06-02 Create README.md
    Folder 01 USV_drive_PCB_Project added

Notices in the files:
parts and their libraries:
Eagle_WR-PHD: Copyright: Würth Elektronik
